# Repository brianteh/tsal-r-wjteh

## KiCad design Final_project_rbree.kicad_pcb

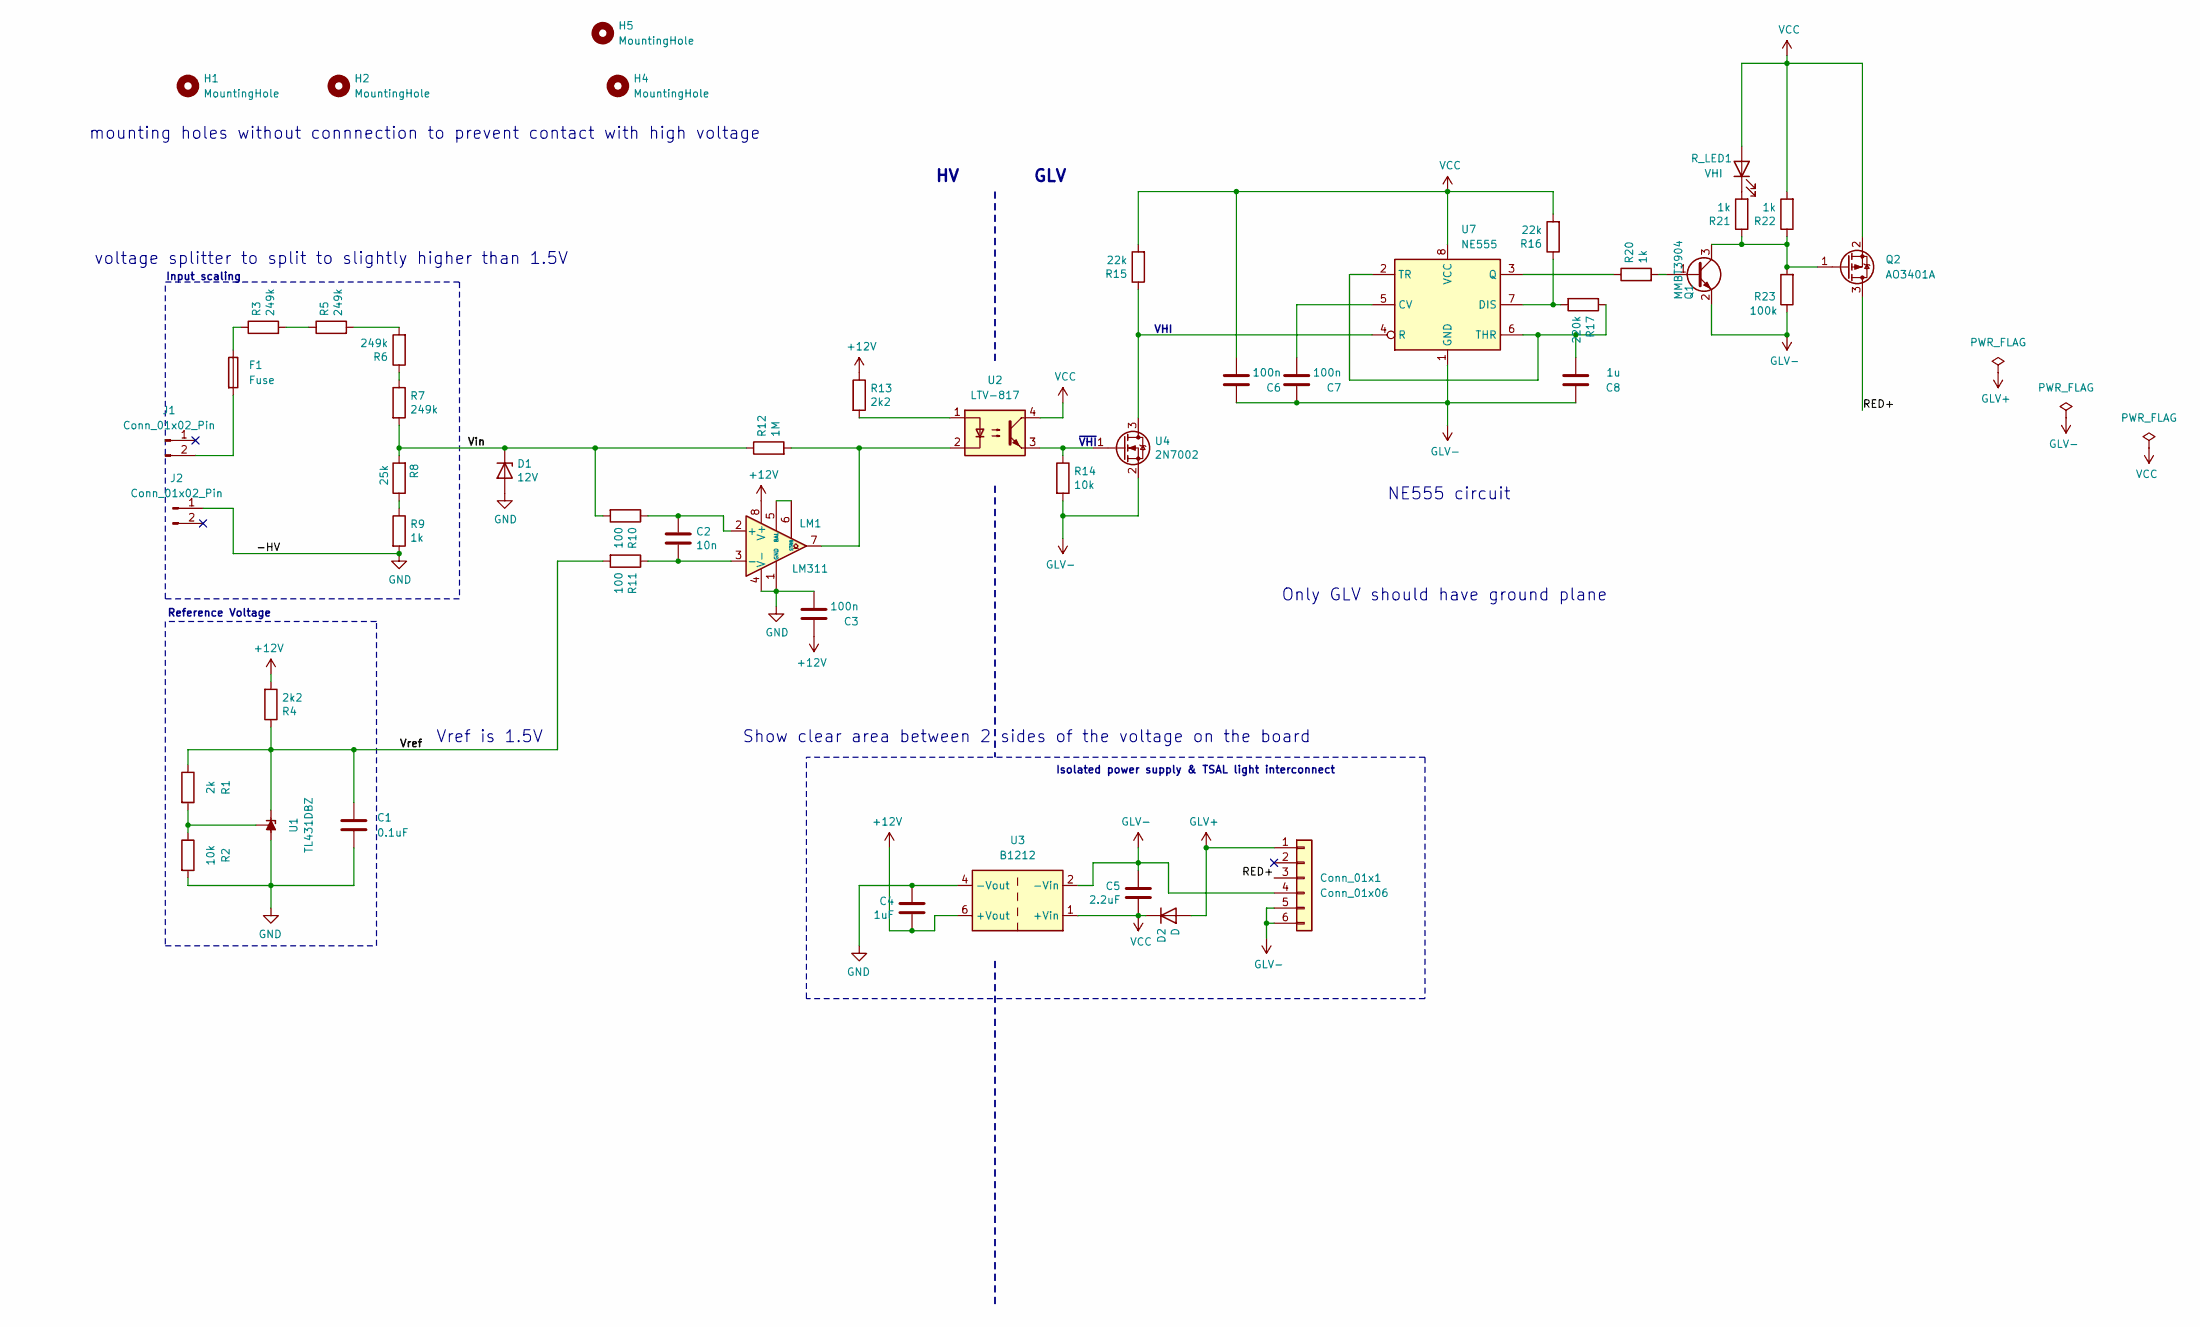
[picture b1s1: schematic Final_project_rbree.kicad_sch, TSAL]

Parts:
C1: 0.1uF; C_1206_3216Metric_Pad1.33x1.80mm_HandSolder
C2: 10n; C_1206_3216Metric_Pad1.33x1.80mm_HandSolder
C3, C6, C7: 100n; C_1206_3216Metric_Pad1.33x1.80mm_HandSolder
C4: 1uF; C_1206_3216Metric_Pad1.33x1.80mm_HandSolder
C5: 2.2uF; C_1206_3216Metric_Pad1.33x1.80mm_HandSolder
C8: 1u; C_1206_3216Metric_Pad1.33x1.80mm_HandSolder
Conn_01x1: Conn_01x06; JST_VH_B6P-VH_1x06_P3.96mm_Vertical
D1: 12V; D_DO-35_SOD27_P7.62mm_Horizontal
D2: D; D_SMA
F1: Fuse; Fuse_1206_3216Metric_Pad1.42x1.75mm_HandSolder
H1, H2, H4, H5: MountingHole; MountingHole_3.2mm_M3
J1, J2: Conn_01x02_Pin; AMASS_XT60-M_1x02_P7.20mm_Vertical
LM1: LM311; SOIC-8_3.9x4.9mm_P1.27mm
Q1: MMBT3904; SOT-23
Q2: AO3401A; SOT-23
R1: 2k; R_1206_3216Metric_Pad1.30x1.75mm_HandSolder
R2, R14: 10k; R_1206_3216Metric_Pad1.30x1.75mm_HandSolder
R3, R5, R6, R7: 249k; R_1206_3216Metric_Pad1.30x1.75mm_HandSolder
R4, R13: 2k2; R_1206_3216Metric_Pad1.30x1.75mm_HandSolder
R8: 25k; R_1206_3216Metric_Pad1.30x1.75mm_HandSolder
R9, R20, R21, R22: 1k; R_1206_3216Metric_Pad1.30x1.75mm_HandSolder
R10, R11: 100; R_1206_3216Metric_Pad1.30x1.75mm_HandSolder
R12: 1M; R_1206_3216Metric_Pad1.30x1.75mm_HandSolder
R15, R16: 22k; R_1206_3216Metric_Pad1.30x1.75mm_HandSolder
R17: 220k; R_1206_3216Metric_Pad1.30x1.75mm_HandSolder
R23: 100k; R_1206_3216Metric_Pad1.30x1.75mm_HandSolder
R_LED1: VHI; LED_D1.8mm_W3.3mm_H2.4mm
U1: TL431DBZ; SOT-23
U2: LTV-817; DIP-4_W8.89mm_SMDSocket_LongPads
U3: B1212; Converter_DCDC_TRACO_TBA2-xxxx_Single_THT
U4: 2N7002; SOT-23
U7: NE555; SOIC-8_3.9x4.9mm_P1.27mm

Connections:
+12V: C3.1, C4.2, LM1.8 (V+), R4.2, R13.1, U3.6 (+Vout)
/RED+: Conn_01x1.3, Q2.3 (D)
/Vin: D1.1 (K), R7.2, R8.2, R10.2, R12.1
/Vref: C1.1, R1.1, R4.1, R11.2, U1.1 (K)
GLV+: Conn_01x1.1, D2.2 (A)
GLV-: C5.1, C6.1, C7.1, C8.1, Conn_01x1.4, Conn_01x1.5, Conn_01x1.6, Q1.2 (E), R14.2, R23.1, U3.2 (-Vin), U4.2 (S), U7.1 (GND)
GND: C1.2, C3.2, C4.1, D1.2 (A), J2.1, LM1.1 (GND), LM1.4 (V-), R2.2, R9.2, U1.3 (A), U3.4 (-Vout)
unnamed: F1.1, R3.1
unnamed: F1.2, J1.2
unnamed: C2.1, LM1.2 (+), R10.1
unnamed: C2.2, LM1.3 (-), R11.1
unnamed: LM1.5 (BAL), LM1.6 (STRB)
unnamed: LM1.7, R12.2, U2.2
unnamed: Q1.1 (B), R20.2
unnamed: Q1.3 (C), Q2.1 (G), R21.1, R22.1, R23.2
unnamed: R3.2, R5.1
unnamed: R5.2, R6.2
unnamed: R6.1, R7.1
unnamed: R8.1, R9.1
unnamed: R13.2, U2.1
unnamed: R21.2, R_LED1.1 (K)
unnamed: R1.2, R2.1, U1.2 (REF)
unnamed: R15.1, U4.3 (D), U7.4 (R)
unnamed: R14.1, U2.3, U4.1 (G)
unnamed: C7.2, U7.5 (CV)
unnamed: R16.1, R17.2, U7.7 (DIS)
unnamed: R20.1, U7.3 (Q)
unnamed: C8.2, R17.1, U7.2 (TR), U7.6 (THR)
VCC: C5.2, C6.2, D2.1 (K), Q2.2 (S), R15.2, R16.2, R22.2, R_LED1.2 (A), U2.4, U3.1 (+Vin), U7.8 (VCC)

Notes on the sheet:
voltage splitter to split to slightly higher than 1.5V
Show clear area between 2 sides of the voltage on the board
Isolated power supply & TSAL light interconnect
Reference Voltage
~{VHI}
mounting holes without connnection to prevent contact with high voltage
Input scaling
Only GLV should have ground plane
GLV
VHI
Vref is 1.5V
NE555 circuit

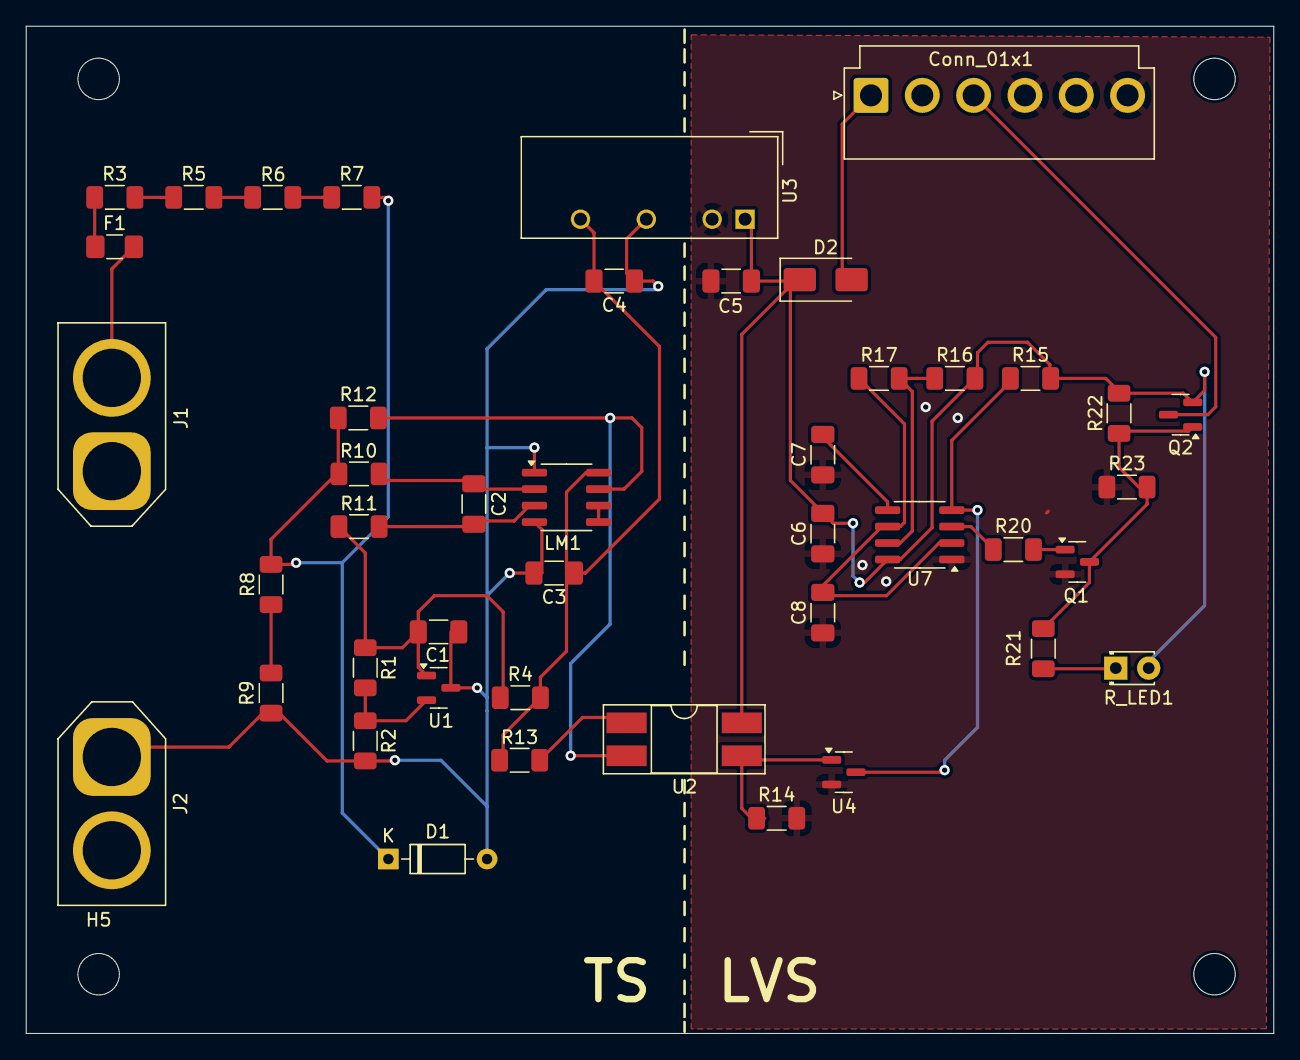
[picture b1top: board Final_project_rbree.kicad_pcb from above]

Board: 2 copper layers, 96.3 x 77.7 mm, 48 parts (0 on the bottom side), 29 nets.

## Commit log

2025-01-21 first comit
2025-01-25 added mounting holes positioning dimension, spacing of R15 R16R17 fixed
2025-02-02 fixed messy TS
2025-02-07 minor ifx
